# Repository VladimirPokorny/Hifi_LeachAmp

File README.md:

# Hifi_LeachAmp

Design of low frequency audio amplifier designed by Prof. Leach from Georgia Institute of Technology.
Main resource: https://leachlegacy.ece.gatech.edu/lowtim/

The PCB is designated in freeware software KiCAD. https://www.kicad.org/

The project is not finished yet. It has been put on hold due to work on the Master's thesis.

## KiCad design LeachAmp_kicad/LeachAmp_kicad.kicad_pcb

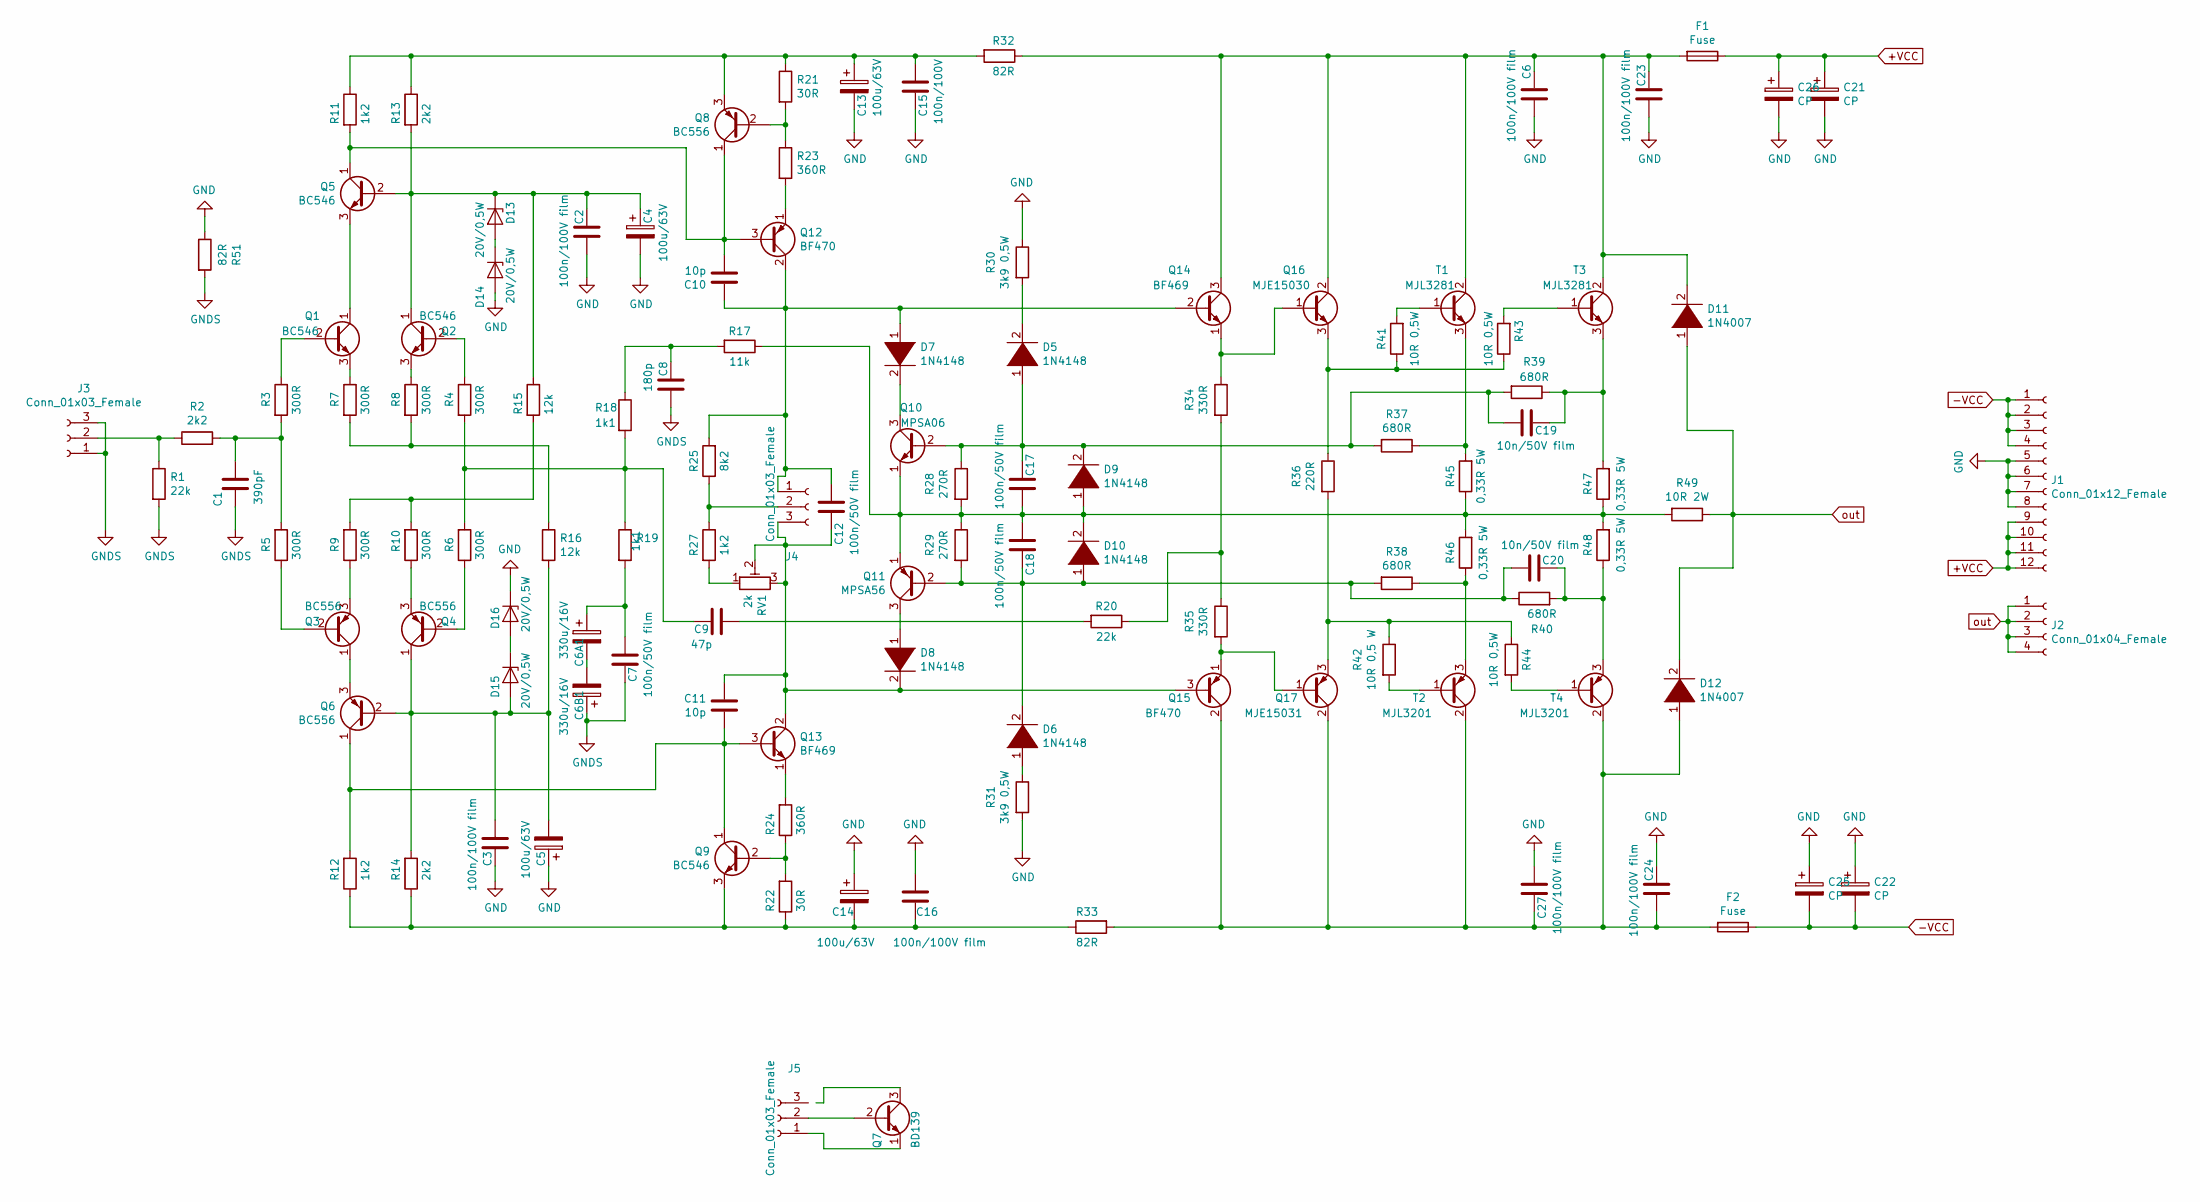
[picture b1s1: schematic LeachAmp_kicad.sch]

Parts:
C1: 390pF; C_Disc_D6.0mm_W2.5mm_P5.00mm
C2, C3, C6, C16, C23, C24, C27: 100n/100V film; C_Rect_L10.0mm_W2.5mm_P7.50mm_MKS4
C4, C5, C13, C14: 100u/63V; CP_Radial_D10.0mm_P5.00mm
C6A1, C6B1: 330u/16V; CP_Radial_D10.0mm_P5.00mm
C7, C12, C17, C18: 100n/50V film; C_Rect_L10.0mm_W2.5mm_P7.50mm_MKS4
C8: 180p; C_Disc_D6.0mm_W2.5mm_P5.00mm
C9: 47p; C_Disc_D6.0mm_W2.5mm_P5.00mm
C10, C11: 10p; C_Disc_D6.0mm_W2.5mm_P5.00mm
C15: 100n/100V; C_Rect_L10.0mm_W2.5mm_P7.50mm_MKS4
C19, C20: 10n/50V film; C_Rect_L7.2mm_W2.5mm_P5.00mm_FKS2_FKP2_MKS2_MKP2
C21, C22, C25, C26: CP; CP_Radial_D35.0mm_P10.00mm_SnapIn
D5, D6, D7, D8, D9, D10: 1N4148; D_DO-35_SOD27_P10.16mm_Horizontal
D11, D12: 1N4007; D_DO-41_SOD81_P10.16mm_Horizontal
D13, D14, D15, D16: 20V/0,5W; D_DO-41_SOD81_P10.16mm_Horizontal
F1, F2: Fuse; Fuseholder5x20_horiz_SemiClosed_Casing10x25mm
J1: Conn_01x12_Female; Wago-256-406
J2: Conn_01x04_Female; Wago-256-402
J3, J4, J5: Conn_01x03_Female; Molex_KK-254_AE-6410-03A_1x03_P2.54mm_Vertical
Q1, Q2, Q5, Q9: BC546; TO-92_Inline
Q3, Q4, Q6, Q8: BC556; TO-92_Inline
Q7: BD139; TO-92_Inline
Q10: MPSA06; TO-92_Inline
Q11: MPSA56; TO-92_Inline
Q12: BF470; TO-126-3_Vertical
Q13: BF469; TO-126-3_Vertical
Q14: BF469; TO-126-3_Horizontal_TabDown
Q15: BF470; TO-126-3_Horizontal_TabDown
Q16: MJE15030; TO-220-3_Horizontal_TabDown
Q17: MJE15031; TO-220-3_Horizontal_TabDown
R1, R20: 22k; R_Axial_DIN0207_L6.3mm_D2.5mm_P10.16mm_Horizontal
R2, R13, R14: 2k2; R_Axial_DIN0207_L6.3mm_D2.5mm_P10.16mm_Horizontal
R3, R4, R5, R6, R7, R8, R9, R10: 300R; R_Axial_DIN0207_L6.3mm_D2.5mm_P10.16mm_Horizontal
R11, R12, R27: 1k2; R_Axial_DIN0207_L6.3mm_D2.5mm_P10.16mm_Horizontal
R15, R16: 12k; R_Axial_DIN0207_L6.3mm_D2.5mm_P10.16mm_Horizontal
R17: 11k; R_Axial_DIN0207_L6.3mm_D2.5mm_P10.16mm_Horizontal
R18, R19: 1k1; R_Axial_DIN0207_L6.3mm_D2.5mm_P10.16mm_Horizontal
R21, R22: 30R; R_Axial_DIN0207_L6.3mm_D2.5mm_P10.16mm_Horizontal
R23, R24: 360R; R_Axial_DIN0207_L6.3mm_D2.5mm_P10.16mm_Horizontal
R25: 8k2; R_Axial_DIN0207_L6.3mm_D2.5mm_P10.16mm_Horizontal
R28, R29: 270R; R_Axial_DIN0207_L6.3mm_D2.5mm_P10.16mm_Horizontal
R30, R31: 3k9 0,5W; R_Axial_DIN0411_L9.9mm_D3.6mm_P15.24mm_Horizontal
R32, R33, R51: 82R; R_Axial_DIN0207_L6.3mm_D2.5mm_P10.16mm_Horizontal
R34, R35: 330R; R_Axial_DIN0207_L6.3mm_D2.5mm_P10.16mm_Horizontal
R36: 220R; R_Axial_DIN0207_L6.3mm_D2.5mm_P10.16mm_Horizontal
R37, R38, R39, R40: 680R; R_Axial_DIN0207_L6.3mm_D2.5mm_P10.16mm_Horizontal
R41, R43, R44: 10R 0,5W; R_Axial_DIN0411_L9.9mm_D3.6mm_P15.24mm_Horizontal
R42: 10R 0,5 W; R_Axial_DIN0411_L9.9mm_D3.6mm_P15.24mm_Horizontal
R45, R46, R47, R48: 0,33R 5W; R_Axial_DIN0617_L17.0mm_D6.0mm_P20.32mm_Horizontal
R49: 10R 2W; R_Axial_DIN0516_L15.5mm_D5.0mm_P20.32mm_Horizontal
RV1: 2k; Potentiometer_Bourns_3266W_Vertical
T1, T3: MJL3281; TO-264-3_Horizontal_TabDown
T2, T4: MJL3201; TO-264-3_Horizontal_TabDown

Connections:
+VCC: C21.1, C26.1, F1.1, J1.9, J1.10, J1.11, J1.12
-VCC: C22.2, C25.2, F2.1, J1.1, J1.2, J1.3, J1.4
GND: C2.1, C3.1, C4.2, C5.1, C6.1, C13.2, C14.1, C15.2, C16.1, C21.2, C22.1, C23.1, C24.2, C25.1, C26.2, C27.1, D14.2 (A), D16.1 (K), J1.5, J1.6, J1.7, J1.8, R30.1, R31.2, R51.1
GNDS: C1.1, C6B1.1, C7.2, C8.2, J3.1, J3.3, R1.2, R51.2
unnamed: C1.2, R2.2, R3.2, R5.2
unnamed: C2.2, C4.1, D13.1 (K), Q2.1 (C), Q5.2 (B), R13.2, R15.1
unnamed: C3.2, C5.2, D15.2 (A), Q4.1 (C), Q6.2 (B), R14.2, R16.2
unnamed: C6A1.1, C7.1, R19.2
unnamed: C6A1.2, C6B1.2
unnamed: C8.1, R17.2, R18.1
unnamed: C9.1, R4.2, R6.2, R18.2, R19.1
unnamed: C9.2, R20.2
unnamed: C10.1, C12.2, D7.1 (K), J4.1, Q12.2 (C), Q14.2 (B), R25.2
unnamed: C10.2, Q5.1 (C), Q8.1 (C), Q12.3 (B), R11.2
unnamed: C11.1, C12.1, D8.2 (A), J4.3, Q13.2 (C), Q15.3 (B), RV1.2, RV1.3
unnamed: C11.2, Q6.1 (C), Q9.1 (C), Q13.3 (B), R12.2
unnamed: C13.1, C15.1, Q8.3 (E), R11.1, R13.1, R21.1, R32.2
unnamed: C14.2, C16.2, Q9.3 (E), R12.1, R14.1, R22.1, R33.1
unnamed: C17.1, C18.2, D9.1 (K), D10.2 (A), Q10.1 (E), Q11.1 (E), R17.1, R28.2, R29.1, R45.1, R46.2, R47.1, R48.2, R49.2
unnamed: C17.2, C19.2, D5.1 (K), D9.2 (A), Q10.2 (B), R28.1, R37.2, R39.2
unnamed: C18.1, C20.1, D6.2 (A), D10.1 (K), Q11.2 (B), R29.2, R38.2, R40.1
unnamed: C19.1, R39.1, R47.2, T3.3 (E)
unnamed: C20.2, R40.2, R48.1, T4.3 (E)
unnamed: C6.2, C23.2, D11.2 (A), F1.2, Q14.3 (C), Q16.2 (C), R32.1, T1.2 (C), T3.2 (C)
unnamed: C24.1, C27.2, D12.1 (K), F2.2, Q15.2 (C), Q17.2 (C), Q17.4 (C), R33.2, T2.2 (C), T2.4 (C), T4.2 (C), T4.4 (C)
unnamed: D5.2 (A), R30.2
unnamed: D6.1 (K), R31.1
unnamed: D7.2 (A), Q10.3 (C)
unnamed: D8.1 (K), Q11.3 (C)
unnamed: D13.2 (A), D14.1 (K)
unnamed: D15.1 (K), D16.2 (A)
unnamed: J3.2, R1.1, R2.1
unnamed: J4.2, R25.1, R27.1
unnamed: J5.1, Q7.1 (E)
unnamed: J5.2, Q7.2 (B)
unnamed: Q1.1 (C), Q5.3 (E)
unnamed: Q1.2 (B), R3.1
unnamed: Q1.3 (E), R7.1
unnamed: Q2.2 (B), R4.1
unnamed: Q2.3 (E), R8.1
unnamed: Q3.1 (C), Q6.3 (E)
unnamed: Q3.2 (B), R5.1
unnamed: Q3.3 (E), R9.1
unnamed: Q4.2 (B), R6.1
unnamed: Q4.3 (E), R10.1
unnamed: Q8.2 (B), R21.2, R23.1
unnamed: Q9.2 (B), R22.2, R24.1
unnamed: Q12.1 (E), R23.2
unnamed: Q13.1 (E), R24.2
unnamed: Q14.1 (E), Q16.1 (B), R34.1
unnamed: Q15.1 (E), Q17.1 (B), R35.2
unnamed: Q16.3 (E), R36.1, R41.1, R43.1
unnamed: Q17.3 (E), R36.2, R42.1, R44.1
unnamed: R9.2, R10.2, R15.2
unnamed: R7.2, R8.2, R16.1
unnamed: R20.1, R34.2, R35.1
unnamed: R27.2, RV1.1
unnamed: R37.1, R45.2, T1.3 (E)
unnamed: R38.1, R46.1, T2.3 (E)
unnamed: R41.2, T1.1 (B)
unnamed: R42.2, T2.1 (B)
unnamed: R43.2, T3.1 (B)
unnamed: R44.2, T4.1 (B)
out: D11.1 (K), D12.2 (A), J2.1, J2.2, J2.3, J2.4, R49.1

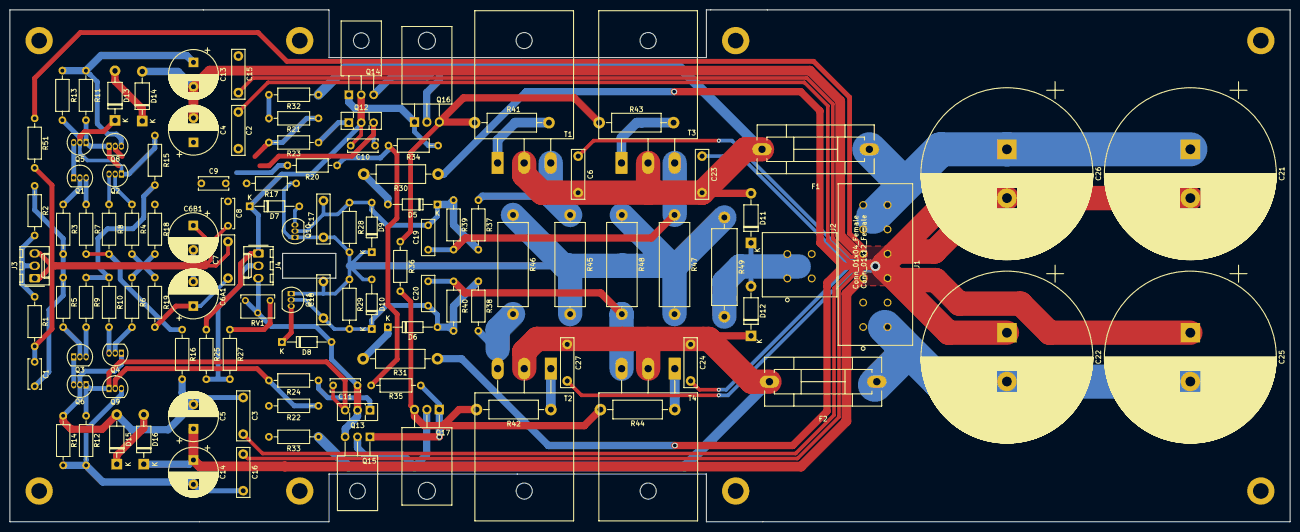
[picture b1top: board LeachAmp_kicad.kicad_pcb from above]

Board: 2 copper layers, 262.4 x 104.9 mm, 124 parts (0 on the bottom side), 62 nets.

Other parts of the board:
 : MountingHole_3.2mm_M3_DIN965_Pad
 #2,  #3,  #4,  #5,  #6,  #7,  #8: MountingHole_3.2mm_M3_DIN965_Pad

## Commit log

2021-01-07 Schéma komplet + DPS v progresu
    Kompletní schéma Leach verze.
    DPS rozpracované - silová část
2021-01-08 DPS progress 70%
    DPS z většiny zpracovaná:
    Výkonová část 85 %;
    signální 60 %;
    zpětná vazba 20 %.
2021-01-08 3D návrh
    Doplněn 3D návrh přední, zadní, strany, chladičů
2021-01-09 DPS progress 90 %
    DPS z většiny zpracovaná:
    Výkonová část 85 %;
    signální 80 %;
    zpětná vazba 40 %.
2021-01-10 DPS 100%
2021-01-10 DPS + rozpiska
2021-01-12 DPS dokončeno
2021-01-13 Dokumentace
2021-01-21 Kondenzatory v prostred
2021-01-28 Opraveny Tranzistory
    Opraveny Tranzistory
2021-01-28 Opraveny Tranzistory
2021-03-01 oprava tranzistoru
2021-05-06 oprava DPS po vymene tranzistoru
2021-05-07 ladeni-DPS
2021-05-07 100% DPS
2021-05-07 pridana rozpiska materiálu
2021-05-20 nove_rozmery_soucastek
    Nové rozměry součástek hlavně u kondenzátorů
2021-05-20 nova_Lakatosi_verze
2021-05-20 verze 20.5.
2021-05-20 oprava DPS

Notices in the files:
parts and their libraries:
Copyright 2016 Accelerated Designs. All rights reserved.
